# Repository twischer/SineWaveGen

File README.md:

SineWaveGen
===========

Messungen
===========

Gemessen wurde der benötigte Strom für die 12V-Versorgung

Bei Verwendung des Sinus-Generators
Ohne Zwischenkreisspannung:		10,6 mA
Mit Zwischenkreisspannung:		8 mA

Bei Verwendung des Trapez-Generators
Ohne Zwischenkreisspannung:		11,3 mA
Mit Zwischenkreisspannung:		7,5 mA

Leistungsaufnahme mit 99W (0,42A) Glühlampe
Trapez-Generator:				120W (0,51A)

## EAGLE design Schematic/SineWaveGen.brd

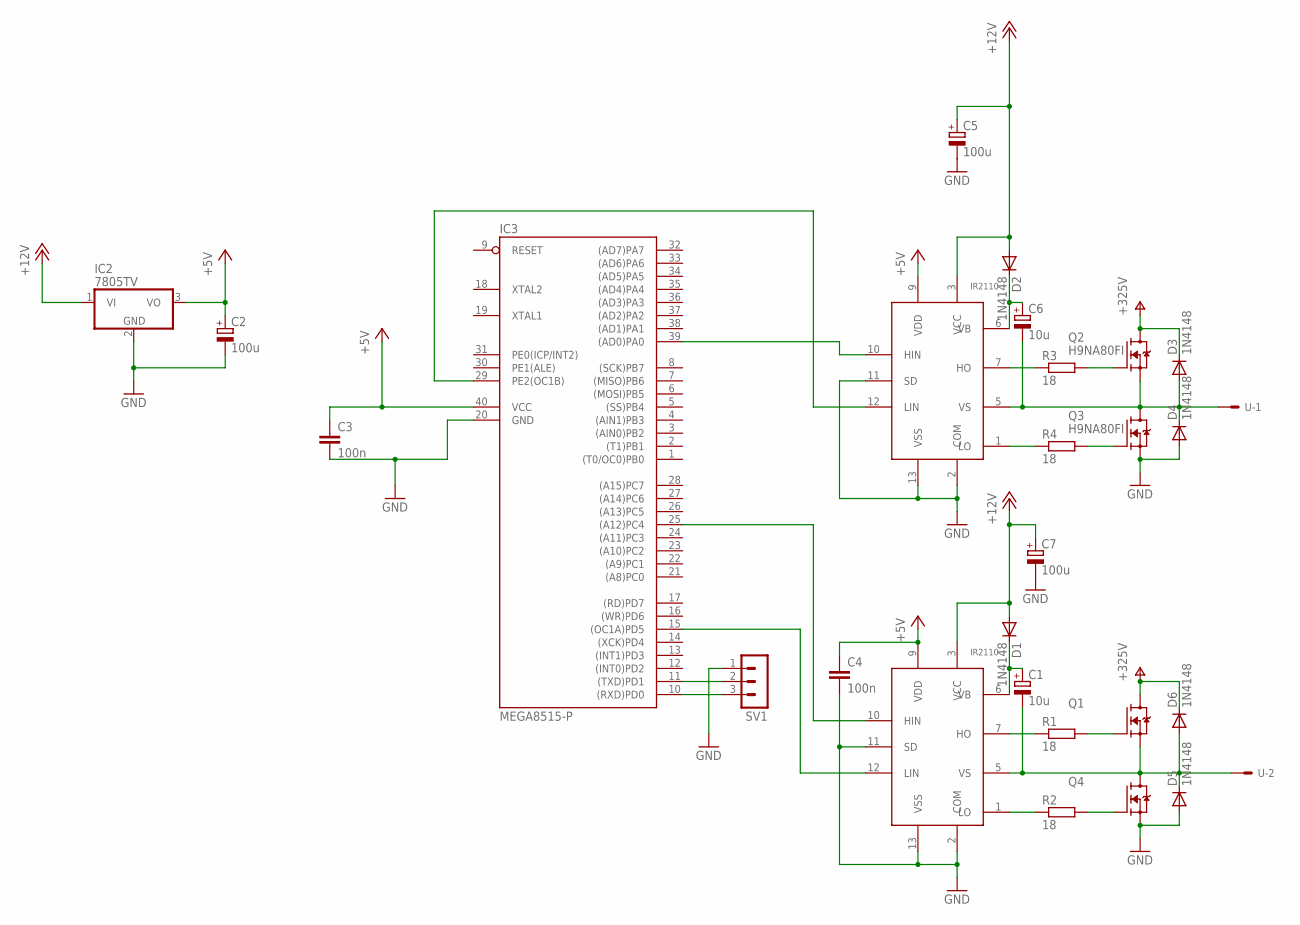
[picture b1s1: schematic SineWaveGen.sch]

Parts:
C1, C6: 10u; E2,5-7
C2, C5, C7: 100u; E2,5-7
C3, C4: 100n; C050-035X075
D1, D2, D3, D4, D5, D6: 1N4148; DO35-7
IC2: 7805TV; TO220V
IC3: MEGA8515-P; DIL40
Q1, Q4: SPW47N60S5; P-TO247
Q2, Q3: H9NA80FI; P-TO247
R1, R2, R3, R4: 18; 0207/12
SV1: MA03-1
U: 5566-2
U$1, U$2: IR2110; DIL14

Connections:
+5V: C2.+, C3.1, C4.1, IC2.3 (VO), IC3.40 (VCC), U$1.9 (VDD), U$2.9 (VDD)
+12V: C5.+, C7.+, D1.A, D2.A, IC2.1 (VI), U$1.3 (VCC), U$2.3 (VCC)
GND: C2.-, C3.2, C4.2, C5.-, C7.-, D4.A, D5.A, IC2.2 (GND), IC3.20 (GND), Q3.3 (S), Q4.3 (S), SV1.1, U$1.2 (COM), U$1.11 (SD), U$1.13 (VSS), U$2.2 (COM), U$2.11 (SD), U$2.13 (VSS)
unnamed: Q1.1 (G), R1.2
unnamed: IC3.39 ((AD0)PA0), U$2.10 (HIN)
unnamed: IC3.15 ((OC1A)PD5), U$1.12 (LIN)
unnamed: IC3.25 ((A12)PC4), U$1.10 (HIN)
unnamed: R2.1, U$1.1 (LO)
unnamed: C1.-, D5.C, D6.A, Q1.3 (S), Q4.2 (D), U.2, U$1.5 (VS)
unnamed: C1.+, D1.C, U$1.6 (VB)
unnamed: Q4.1 (G), R2.2
unnamed: R1.1, U$1.7 (HO)
unnamed: IC3.11 ((TXD)PD1), SV1.2
unnamed: IC3.10 ((RXD)PD0), SV1.3
unnamed: IC3.29 (PE2(OC1B)), U$2.12 (LIN)
unnamed: R3.1, U$2.7 (HO)
unnamed: Q2.1 (G), R3.2
unnamed: R4.1, U$2.1 (LO)
unnamed: Q3.1 (G), R4.2
unnamed: C6.-, D3.A, D4.C, Q2.3 (S), Q3.2 (D), U.1, U$2.5 (VS)
unnamed: C6.+, D2.C, U$2.6 (VB)
V+: D3.C, D6.C, Q1.2 (D), Q2.2 (D)

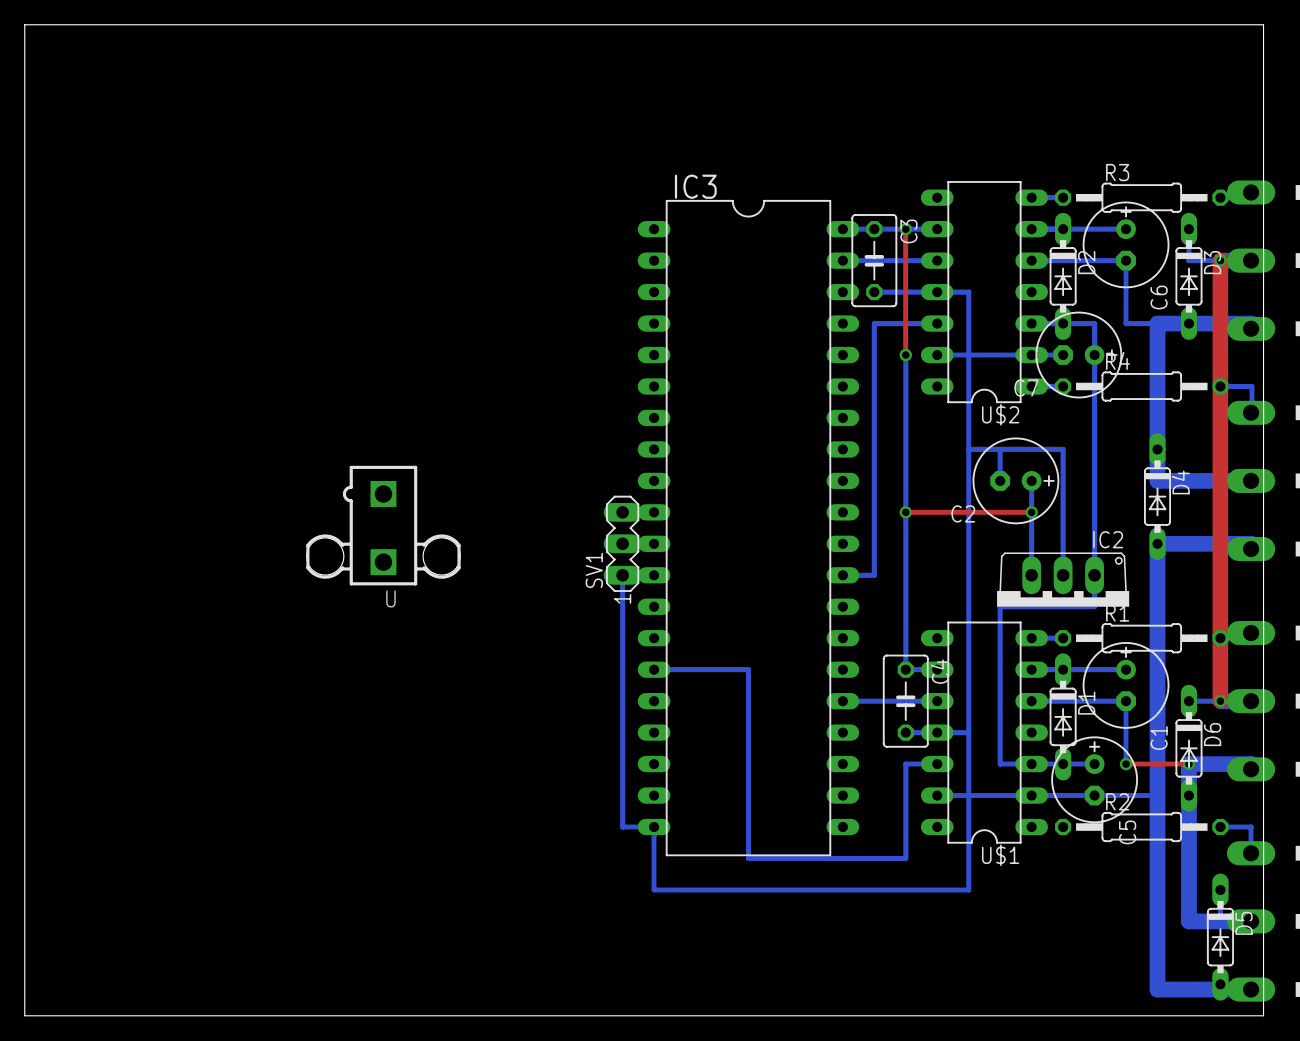
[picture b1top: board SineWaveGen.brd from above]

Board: 2 copper layers, 100.0 x 80.0 mm, 27 parts (0 on the bottom side), 22 nets.

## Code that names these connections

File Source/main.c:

#include <stdint.h>
#include <stdbool.h>

#include <avr/io.h>
#include <avr/interrupt.h>
#include <avr/wdt.h>

#include <util/delay.h>


#define BRIDGE1_HIGH_DDR		DDRA
#define BRIDGE1_HIGH_PORT		PORTA
#define BRIDGE1_HIGH_IN			PINA
#define BRIDGE1_HIGH_PIN		PA0

#define BRIDGE1_LOW_DDR			DDRE
#define BRIDGE1_LOW_PORT		PORTE
#define BRIDGE1_LOW_IN			PINE
#define BRIDGE1_LOW_PIN			PE2
#define BRIDGE1_LOW_OCR			OCR1BL


#define BRIDGE2_HIGH_DDR		DDRC
#define BRIDGE2_HIGH_PORT		PORTC
#define BRIDGE2_HIGH_IN			PINC
#define BRIDGE2_HIGH_PIN		PC4

#define BRIDGE2_LOW_DDR			DDRD
#define BRIDGE2_LOW_PORT		PORTD
#define BRIDGE2_LOW_IN			PIND
#define BRIDGE2_LOW_PIN			PD5
#define BRIDGE2_LOW_OCR			OCR1AL


#define OUTPUT_SWITCH_PORT		PORTD
#define OUTPUT_SWITCH_IN		PIND
#define OUTPUT_SWITCH_PIN		PD7




// The time out between a half bridge (in µs)
#define FET_TIMEOUT				3
// length of the v+ and v+ pulse (in ms)
#define PULSE_TIME				7
// length of the null pulse where both outputs are connected to gnd (in ms)
#define NULL_TIME				3



const uint8_t SINE_TABLE[] =  { 0, 21,41,61,81,100,119,136,153,169,184,198,210,221,230,238,245,250,253,255,253,250,245,238,230,221,210,198,184,169,153,136,119,100,81,61,41,21, 0 };


ISR(TIMER1_OVF_vect)
{
	static uint8_t sineTableIndex = 0;
	sineTableIndex++;
	
	static bool positiveHalfWave = true;
	
	if (sineTableIndex >= sizeof(SINE_TABLE))
	{
		positiveHalfWave = !positiveHalfWave;
		sineTableIndex = 0;
		
		// the deadband on each half bridge is given by the switch of in the sien table
		// (the 0 at the end)
		if (positiveHalfWave)
		{
			BRIDGE2_HIGH_PORT &= ~(1<<BRIDGE2_HIGH_PIN);
			BRIDGE1_HIGH_PORT |= (1<<BRIDGE1_HIGH_PIN);
		}
		else
		{
			BRIDGE1_HIGH_PORT &= ~(1<<BRIDGE1_HIGH_PIN);
			BRIDGE2_HIGH_PORT |= (1<<BRIDGE2_HIGH_PIN);
		}
	}
	
	if (positiveHalfWave)
	{
		BRIDGE2_LOW_OCR = SINE_TABLE[sineTableIndex];
		BRIDGE1_LOW_OCR = 0x00;
	}
	else
	{
		BRIDGE2_LOW_OCR = 0x00;
		BRIDGE1_LOW_OCR = SINE_TABLE[sineTableIndex];
	}
}


void switchOutputsOff(void)
{
	// open fets which are conected to v+
	BRIDGE1_HIGH_PORT &= ~(1<<BRIDGE1_HIGH_PIN);
	BRIDGE2_HIGH_PORT &= ~(1<<BRIDGE2_HIGH_PIN);
	
	// clear pwm outputs (open fets which are connected to gnd
	BRIDGE1_LOW_PORT &= ~(1<<BRIDGE1_LOW_PIN);
	BRIDGE2_LOW_PORT &= ~(1<<BRIDGE2_LOW_PIN);
	
	// disable timer and pwm to get control with the port registers to the output pins
	TCCR1A = 0x00;
	TCCR1B = 0x00;
}


void enterSafeMode(void)
{
	switchOutputsOff();
	
	// switch off watchdog to realy wait for reset
	wdt_disable();
	
	// wait for reset
	while (true)
	{
	}
}


void checkOutputConflicts(void)
{
	// switch all outputs off and wait for an avr reset
	// if both outputs of the same half bridge are active at the same time
	const uint8_t bridge1HighOut = BRIDGE1_HIGH_IN;
	const uint8_t bridge1LowOut = BRIDGE1_LOW_IN;
	if (  (bridge1HighOut & (1<<BRIDGE1_HIGH_PIN)) && (bridge1LowOut & (1<<BRIDGE1_LOW_PIN))  )
		enterSafeMode();
	
	const uint8_t bridge2HighOut = BRIDGE2_HIGH_IN;
	const uint8_t bridge2LowOut = BRIDGE2_LOW_IN;
	if (  (bridge2HighOut & (1<<BRIDGE2_HIGH_PIN)) && (bridge2LowOut & (1<<BRIDGE2_LOW_PIN))  )
		enterSafeMode();
	
	// reset watchdog timer
	wdt_reset();
}


void sineGenerator(void)
{
	// configure timer and pwm for sine wave output
	BRIDGE2_LOW_OCR = 0x00;
	BRIDGE1_LOW_OCR = 0x00;
	TCCR1A = (1<<COM1A1) | (1<<COM1B1) | (1<<WGM10);  // Clear on compare and phase correct 8-bit pwm
	TCCR1B = (0<<CS12) | (0<<CS11) | (1<<CS10);     //PRE 1
	TIMSK  = (1<<TOIE1); // enable overflow interrupt
	
	sei();
	
	DDRB = 0xFF;
	
	while(true)
	{
		checkOutputConflicts();
	}
}


void trapezeGenerator(void)
{	
	// otherwise generate a trapez
	// useful to minimize the switching time of the fets (more efficient)
	//				1	2	
	// 		NULL	-	-	!PC4	PD5
	// 		POS		+	-	!PE2	PA0
	// 		NULL	-	-	!PA0	PE2
	//		NEG		-	+	!PD5	PC4
	while (true)
	{
		// 	NULL	-	-	!PC4	PD5
		BRIDGE2_HIGH_PORT &= ~(1<<BRIDGE2_HIGH_PIN);
		_delay_us(FET_TIMEOUT);
		BRIDGE2_LOW_PORT |= (1<<BRIDGE2_LOW_PIN);		// Positiv half wave PWM
		
		checkOutputConflicts();
		_delay_ms(NULL_TIME);
		checkOutputConflicts();
		
		
		// 	POS		+	-	!PE2	PA0
		BRIDGE1_LOW_PORT &= ~(1<<BRIDGE1_LOW_PIN);		// Negativ half wave PWM
		_delay_us(FET_TIMEOUT);
		BRIDGE1_HIGH_PORT |= (1<<BRIDGE1_HIGH_PIN);
		
		checkOutputConflicts();
		_delay_ms(PULSE_TIME);
		checkOutputConflicts();
		
		
		// 	NULL	-	-	!PA0	PE2
		BRIDGE1_HIGH_PORT &= ~(1<<BRIDGE1_HIGH_PIN);
		_delay_us(FET_TIMEOUT);
		BRIDGE1_LOW_PORT |= (1<<BRIDGE1_LOW_PIN);		// Negativ half wave PWM
		
		checkOutputConflicts();
		_delay_ms(NULL_TIME);
		checkOutputConflicts();
		
		
		//		NEG		-	+	!PD5	PC4
		BRIDGE2_LOW_PORT &= ~(1<<BRIDGE2_LOW_PIN);		// Positiv half wave PWM
		_delay_us(FET_TIMEOUT);
		BRIDGE2_HIGH_PORT |= (1<<BRIDGE2_HIGH_PIN);
		
		checkOutputConflicts();
		_delay_ms(PULSE_TIME);
		checkOutputConflicts();
	}
}


int main(void)
{
	switchOutputsOff();
	
	// enable pull up for output switch input
	OUTPUT_SWITCH_PORT |= (1<<OUTPUT_SWITCH_PIN);
	
	BRIDGE1_HIGH_DDR |= (1<<BRIDGE1_HIGH_PIN);
	BRIDGE2_HIGH_DDR |= (1<<BRIDGE2_HIGH_PIN);
	
	// enable PWM outputs
	DDRD |= (1<<PD5);		// Higher half wave PWM
	DDRE |= (1<<PE2);		// Lower half wave PWM
	
	// enable watchdog timer
	wdt_enable(WDTO_15MS);
	
	
	// read output configuration from an jumper or switch
	const bool generateSineOutput = (OUTPUT_SWITCH_IN & (1<<OUTPUT_SWITCH_PIN));
	if (generateSineOutput)
		sineGenerator();
	else
		trapezeGenerator();
	
	return 0;
}

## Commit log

2014-03-25 Add inital sine wave generator (creates 50Hz signal)
2014-03-25 Add schematic for power switches
2014-03-25 Port for atmega8515 and clean debugging code
2014-04-06 use bigger distances for high voltages
2014-05-06 Make it possible to choose a trapez generator
2014-05-06 Sine Wave with auto deadband by sine tabel with 0
2014-05-07 Enter safe mode if high and low side of the same bridge is enabled Use watchdog timer to garent this checks
2014-10-04 Use longer dead time for sine wave generator
